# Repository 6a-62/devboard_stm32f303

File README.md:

# devboard_stm32f303
System development board for the STM32F303CCT6

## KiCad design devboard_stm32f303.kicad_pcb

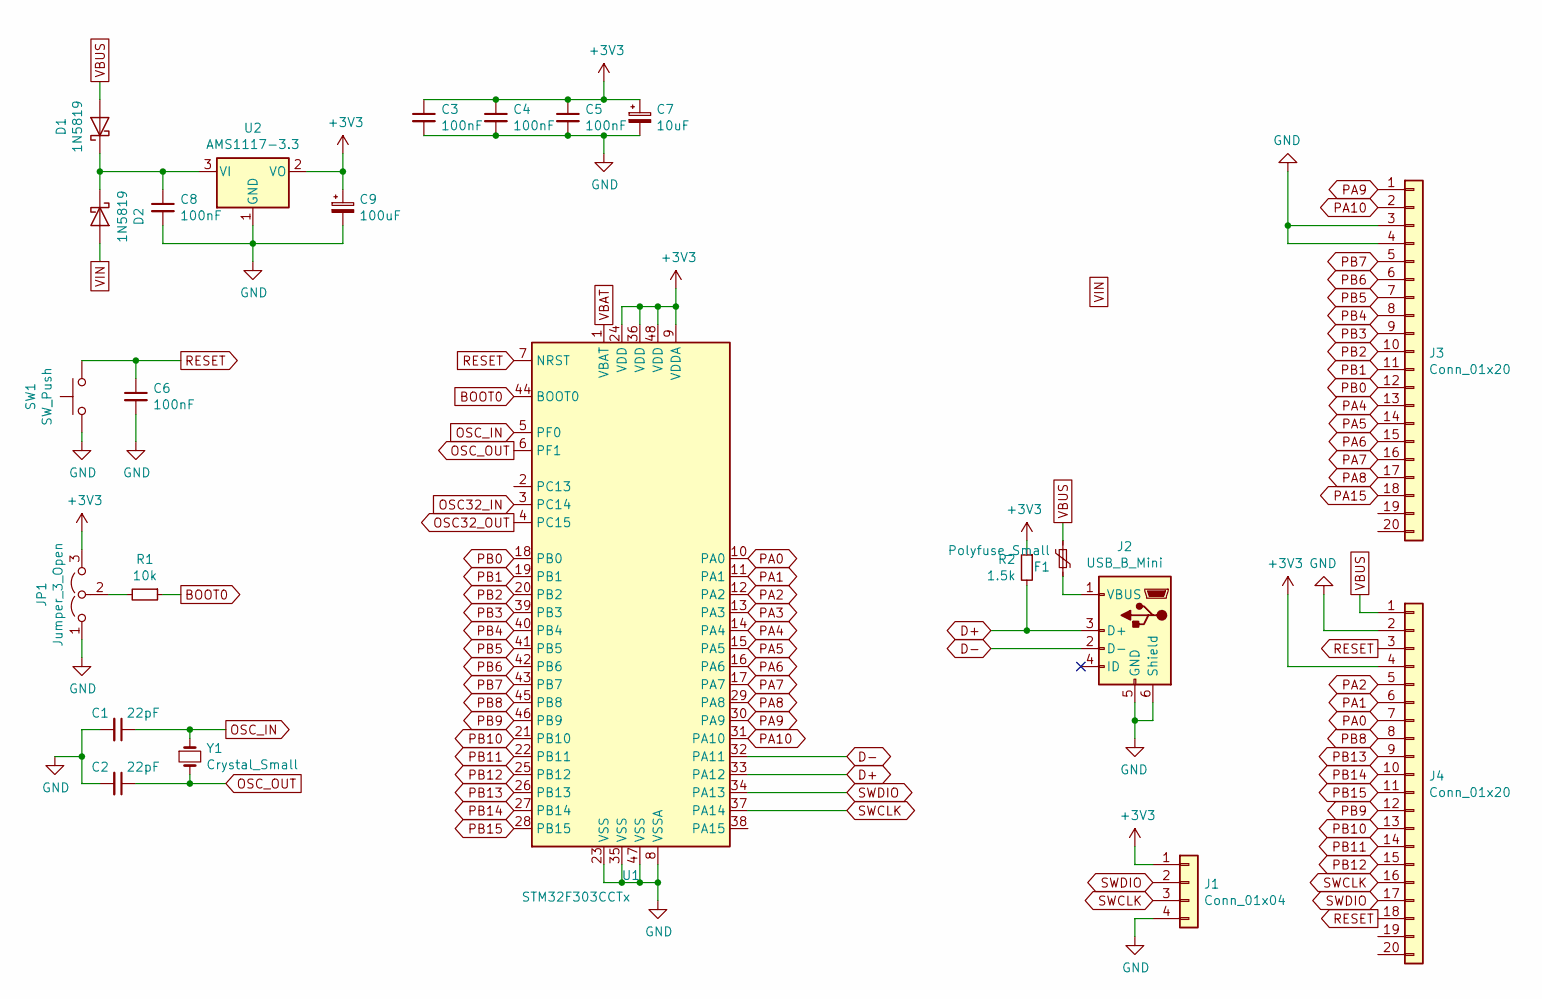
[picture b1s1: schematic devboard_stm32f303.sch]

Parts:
C1, C2: 22pF; C_0805_2012Metric
C3, C4, C5, C6, C8: 100nF; C_0805_2012Metric
C7: 10uF; C_0805_2012Metric
C9: 100uF; CP_EIA-3528-15_AVX-H
D1, D2: 1N5819; D_SOD-123
F1: Polyfuse_Small; Fuse_1206_3216Metric
J1: Conn_01x04; PinHeader_1x04_P2.54mm_Vertical
J2: USB_B_Mini; USB_Mini-B_Lumberg_2486_01_Horizontal
J3, J4: Conn_01x20; PinHeader_1x20_P2.54mm_Vertical
JP1: Jumper_3_Open; PinHeader_1x03_P2.54mm_Vertical
R1: 10k; R_0805_2012Metric
R2: 1.5k; R_0805_2012Metric
SW1: SW_Push; SW_PUSH_6mm
U1: STM32F303CCTx; LQFP-48_7x7mm_P0.5mm
U2: AMS1117-3.3; SOT-223-3_TabPin2
Y1: Crystal_Small; Crystal_SMD_5032-2Pin_5.0x3.2mm

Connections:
+3V3: C3.1, C4.1, C5.1, C7.1, C9.1, J1.1, J4.4, JP1.3 (B), R2.1, U1.9 (VDDA), U1.24 (VDD), U1.36 (VDD), U1.48 (VDD), U2.2 (VO)
BOOT0: R1.1, U1.44 (BOOT0)
D+: J2.3 (D+), R2.2, U1.33 (PA12)
D-: J2.2 (D-), U1.32 (PA11)
GND: C1.2, C2.2, C3.2, C4.2, C5.2, C6.2, C7.2, C8.2, C9.2, J1.4, J2.5 (GND), J2.6 (Shield), J3.3, J3.4, J4.2, JP1.1 (A), SW1.1, U1.8 (VSSA), U1.23 (VSS), U1.35 (VSS), U1.47 (VSS), U2.1 (GND)
unnamed: C8.1, D1.1 (K), D2.1 (K), U2.3 (VI)
unnamed: F1.1, J2.1 (VBUS)
unnamed: JP1.2 (C), R1.2
OSC32_IN: U1.3 (PC14)
OSC32_OUT: U1.4 (PC15)
OSC_IN: C1.1, U1.5 (PF0), Y1.1
OSC_OUT: C2.1, U1.6 (PF1), Y1.2
PA0: J4.7, U1.10 (PA0)
PA1: J4.6, U1.11 (PA1)
PA2: J4.5, U1.12 (PA2)
PA3: U1.13 (PA3)
PA4: J3.13, U1.14 (PA4)
PA5: J3.14, U1.15 (PA5)
PA6: J3.15, U1.16 (PA6)
PA7: J3.16, U1.17 (PA7)
PA8: J3.17, U1.29 (PA8)
PA9: J3.1, U1.30 (PA9)
PA10: J3.2, U1.31 (PA10)
PA15: J3.18
PB0: J3.12, U1.18 (PB0)
PB1: J3.11, U1.19 (PB1)
PB2: J3.10, U1.20 (PB2)
PB3: J3.9, U1.39 (PB3)
PB4: J3.8, U1.40 (PB4)
PB5: J3.7, U1.41 (PB5)
PB6: J3.6, U1.42 (PB6)
PB7: J3.5, U1.43 (PB7)
PB8: J4.8, U1.45 (PB8)
PB9: J4.12, U1.46 (PB9)
PB10: J4.13, U1.21 (PB10)
PB11: J4.14, U1.22 (PB11)
PB12: J4.15, U1.25 (PB12)
PB13: J4.9, U1.26 (PB13)
PB14: J4.10, U1.27 (PB14)
PB15: J4.11, U1.28 (PB15)
RESET: C6.1, J4.3, J4.18, SW1.2, U1.7 (NRST)
SWCLK: J1.3, J4.16, U1.37 (PA14)
SWDIO: J1.2, J4.17, U1.34 (PA13)
VBAT: U1.1 (VBAT)
VBUS: D1.2 (A), F1.2, J4.1
VIN: D2.2 (A)

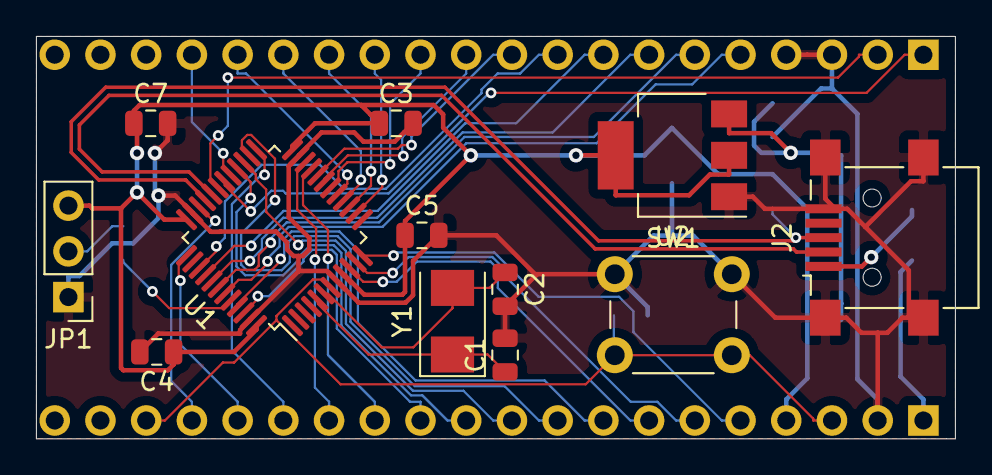
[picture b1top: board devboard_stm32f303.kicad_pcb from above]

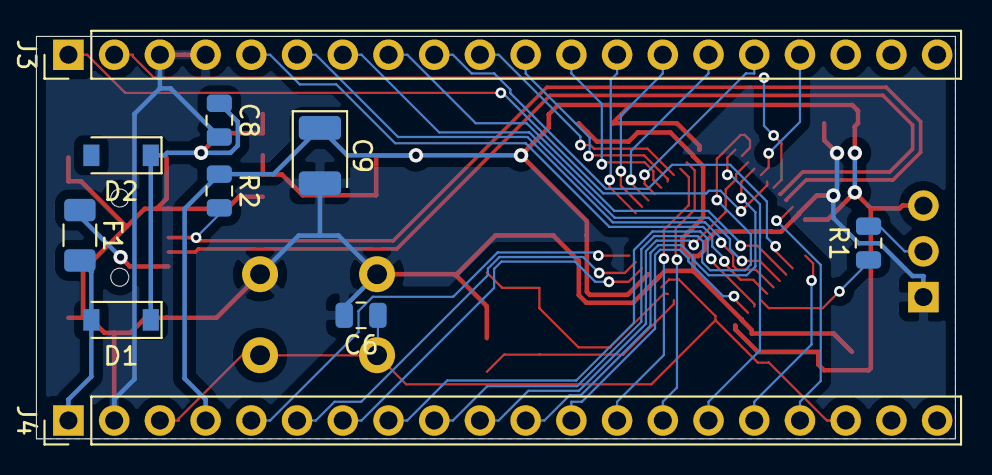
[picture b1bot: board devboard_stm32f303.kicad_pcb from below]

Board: 2 copper layers, 51.1 x 22.4 mm, 22 parts (10 on the bottom side), 40 nets.

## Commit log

2020-01-31 Add files
2020-01-31 Add netlist tags
2020-01-31 Add polyfuse
2020-01-31 Power routing
2020-01-31 Add promicro pinout schematic
2020-02-01 Start new routing
2020-02-01 More routing
2020-02-01 Fix DRC errors
2020-02-01 New board layout
2020-02-01 Basic routing
2020-02-01 Autoroute rest of the board
2020-02-01 Add ground fills
